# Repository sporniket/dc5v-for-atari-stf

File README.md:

# DC5V for the Atari STF

> [WARNING] Please read carefully this note before using this project. It contains important facts.

Content

1. What is **DC5V for the Atari STF**, and when to use it ?
2. What should you know before using **DC5V for the Atari STF** ?
3. How to use **DC5V for the Atari STF** ?
4. Known issues
5. Miscellanous

## 1. What is **DC5V for the Atari STF**, and when to use it ?

**DC5V for the Atari STF** is an alternative pcb to replace the integrated power supply of the Atari STf, based on the premise that the original power plug will receive a DC 5V, 3A to 4A supply instead of being plugged to the main grid (110V to 240V, 50Hz to 60Hz, 1A).

**BOM v1**

|Designator|Description|URL (if appliable)|
|---|---|---|
|J1|**Würth Elektronik** 7.00mm Screwless 45° Entry, Serie 4122, 1×3 – #691412220003|[Mouser 710-691412220003](https://www.mouser.com/ProductDetail/710-691412220003) |
|F1|**Würth Elektronik** Shocksafe Fuse Holder – #696310001002|[Mouser 710-696310001002](https://www.mouser.com/ProductDetail/710-696310001002) |
|SW1|Latching Push Button, on-off Switch, DIP 6 pins (row pitch 6mm, pin pitch 2.5mm, 8×8mm body)|[Aliexpress 1005003333312190](https://www.aliexpress.com/item/1005003333312190.html) |
|J2 - contact|**TE connectivity** Connector Contact, Socket, Wire-to-Board / Wire-to-Wire, 26 – 20 AWG Wire Size, .12 – .5 mm² Wire Size, Tin, Strip, Wire & Cable, 2 A, Signal – #170262-1|[Mouser 571-1702621-CT ](https://www.mouser.com/ProductDetail/571-1702621-CT) |
|J2 - housing|**TE connectivity** Housing, Receptacle, Wire-to-Board, 6 Position, .098in/2.5 mm Centerline, Crimp, 1 Row, Natural, Mating Retention, Wire & Cable, Power & Signal – #171822-6|[Mouser 571-171822-6](https://www.mouser.com/ProductDetail/571-171822-6) |
|J3 - pin sockets|Round socket connector strip|[Exxos #0169](https://www.exxosforum.co.uk/atari/store2/#0169) |
|J3 - pins|Round pin connector strip|[Exxos #0132](https://www.exxosforum.co.uk/atari/store2/#0132) |
|J4|Right angled, pitch 2.54mm, 1×4 pins header|—|
|J5|pitch 2.54mm, 1×2 pins header, classic or JST style|—|

### Licence

**DC5V for the Atari STF** is published under the Creative Commons CC0 license. You can find a copy of the licence there : https://creativecommons.org/publicdomain/zero/1.0/legalcode

You can copy, modify, distribute and perform the work, even for commercial purposes, all without asking permission.

**DC5V for the Atari STF** is distributed in the hope that it will be useful, but WITHOUT ANY WARRANTY; without even the implied warranty of MERCHANTABILITY or FITNESS FOR A PARTICULAR PURPOSE.

### Release notes

## 2. What should you know before using **DC5V for the Atari STF** ?

**DC5V for the Atari STF** is made using Kicad 6.

> Do not use **DC5V for the Atari STF** if this project is not suitable for your project.

## 3. How to use **DC5V for the Atari STF** ?

### From sources

To get the latest available work, one must clone the git repository, build and install the package.

	git clone --recurse-submodules https://github.com/sporniket/dc5v-for-atari-stf.git

Then, open the project with Kicad 6.

## 4. Known issues
See the [project issues](https://github.com/sporniket/dc5v-for-atari-stf/issues) page.

## 5. Miscellanous

### Report issues
Use the [project issues](https://github.com/sporniket/dc5v-for-atari-stf/issues) page.

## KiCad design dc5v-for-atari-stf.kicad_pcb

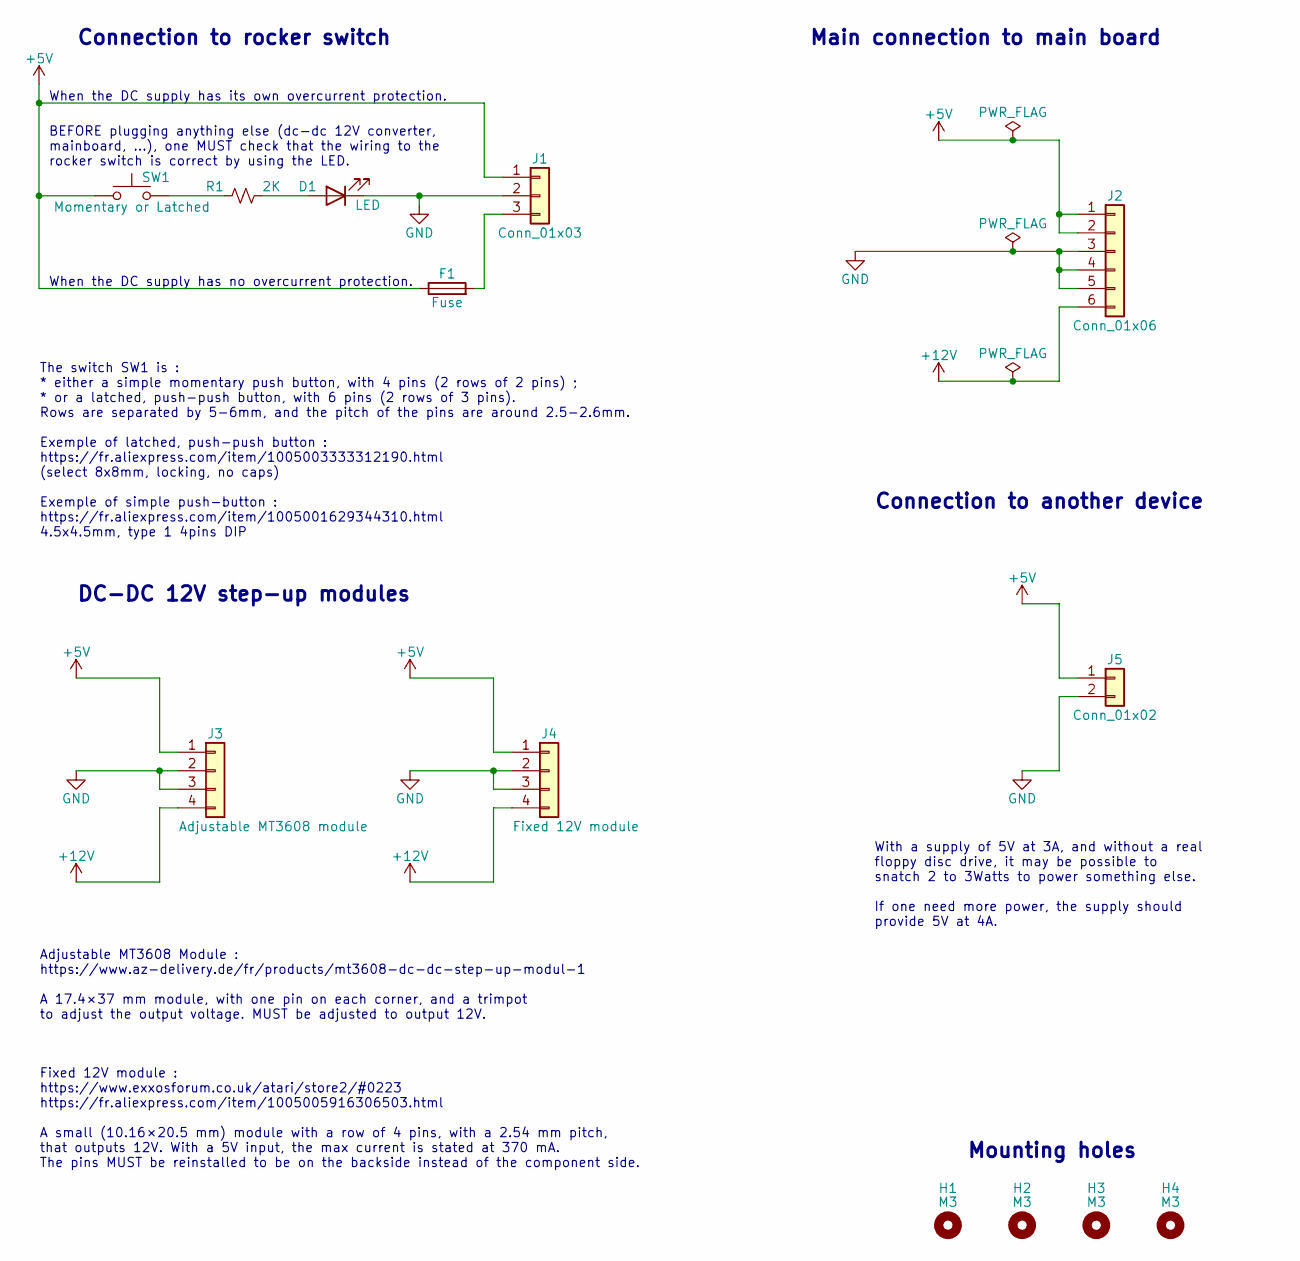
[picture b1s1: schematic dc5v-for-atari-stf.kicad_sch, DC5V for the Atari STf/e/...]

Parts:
D1: LED; LED_D3.0mm
F1: Fuse; FuseHolder_Cylinder_5x20mm_Wurth_Elektronik_696310001002; Mouser part number 710-696310001002
H1, H2, H3, H4: M3; MountingHole_3.5mm
J1: Conn_01x03; Fixed_Terminal_Blocks_Wurth_Elektronik_Serie_4122_7.00mm_Sc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; Mouser part number 710-691412220003
J2: Conn_01x06; PinHeader_1x06_P2.54mm_Vertical
J3: Adjustable MT3608 module; module_mt3608_ajustable_output
J4: Fixed 12V module; module_dc_dc_step_up_12V_W10.16mm_H20.5mm_PinSocket_1x04_P2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
J5: Conn_01x02; PinHeader_1x02_P2.54mm_Vertical
R1: 2K; Passive_THT_resistor_W2.54mm_L12.70mm
SW1: Momentary or Latched; combined_push_button_4pins_X_latched_button_6pins__2rows_W5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

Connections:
+5V: F1.1, J1.1, J2.1, J2.2, J3.1, J4.1, J5.1, SW1.1
+12V: J2.6, J3.4, J4.4
GND: D1.1 (K), J1.2, J2.3, J2.4, J2.5, J3.2, J3.3, J4.2, J4.3, J5.2
unnamed: D1.2 (A), R1.2
unnamed: F1.2, J1.3
unnamed: R1.1, SW1.2

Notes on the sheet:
The switch SW1 is : * either a simple momentary push button, with 4 pins (2 rows of 2 pins) ; * or a latched, push-push button, with 6 pins (2 rows of 3 pins). Rows are separated by 5-6mm, and the pitch of the pins are around 2.5-2.6mm. Exemple of latched, push-push button : https://fr.aliexpress.c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
Mounting holes
With a supply of 5V at 3A, and without a real floppy disc drive, it may be possible to snatch 2 to 3Watts to power something else. If one need more power, the supply should provide 5V at 4A.
DC-DC 12V step-up modules
Connection to rocker switch
BEFORE plugging anything else (dc-dc 12V converter, mainboard, ...), one MUST check that the wiring to the rocker switch is correct by using the LED.
Main connection to main board
When the DC supply has its own overcurrent protection.
Connection to another device
Adjustable MT3608 Module : https://www.az-delivery.de/fr/products/mt3608-dc-dc-step-up-modul-1 A 17.4×37 mm module, with one pin on each corner, and a trimpot to adjust the output voltage. MUST be adjusted to output 12V.
Fixed 12V module : https://www.exxosforum.co.uk/atari/store2/#0223 https://fr.aliexpress.com/item/1005005916306503.html A small (10.16×20.5 mm) module with a row of 4 pins, with a 2.54 mm pitch, that outputs 12V. With a 5V input, the max current is stated at 370 mA. The pins MUST be reinstalled to 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
When the DC supply has no overcurrent protection.

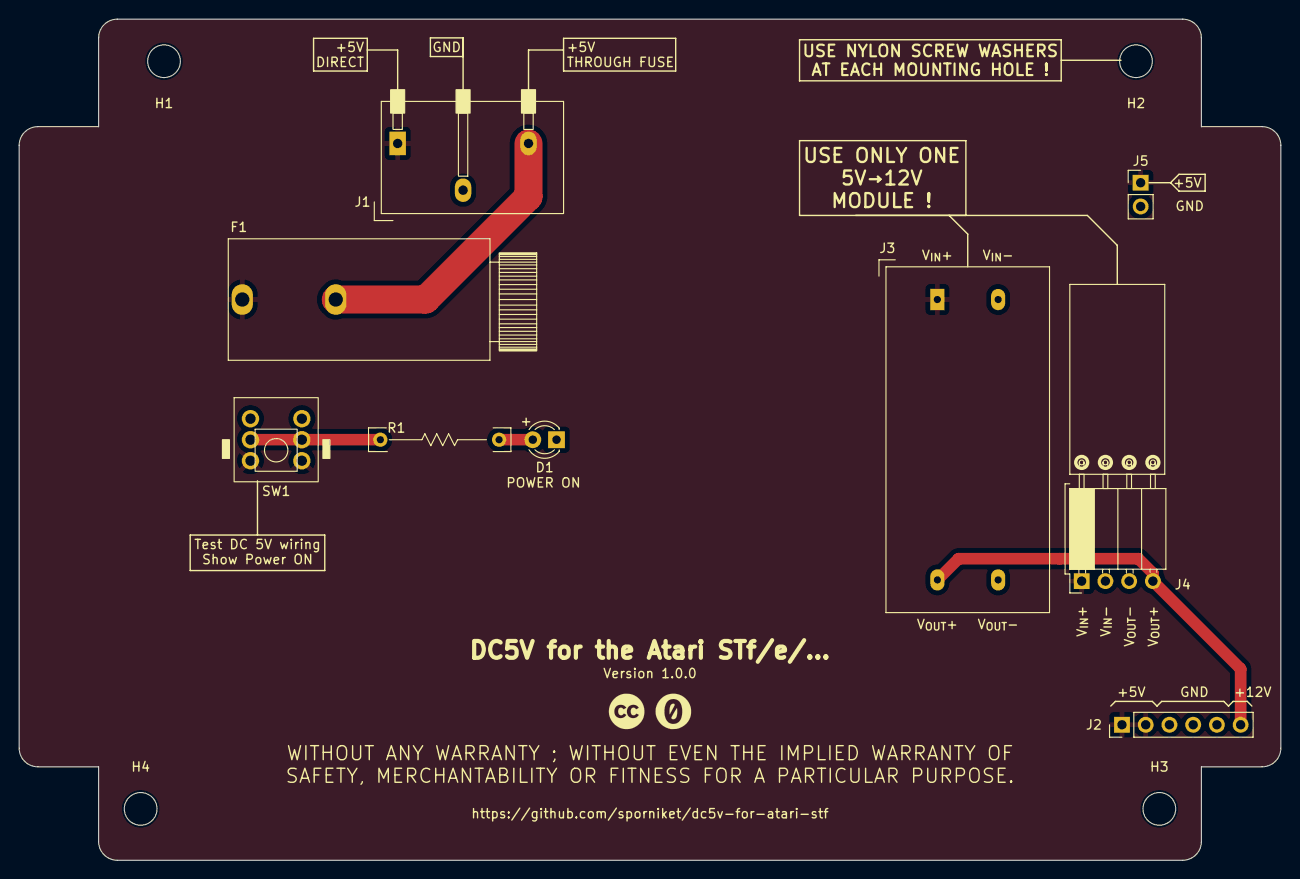
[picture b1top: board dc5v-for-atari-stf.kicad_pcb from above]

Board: 2 copper layers, 135.0 x 90.0 mm, 13 parts (0 on the bottom side), 6 nets.

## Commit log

2023-08-21 update submodules : kicad-symbols-handmade and kicad-footprints-handmade
2023-08-22 init readme
2023-08-22 initialize project
2023-08-22 do the schematic
2023-08-22 metadata of the schematic
2023-08-22 added footprints library for power modules
2023-08-22 Numbers on symbols, add footprint so that SW1 can be either push button or latched push-push button
2023-08-23 update footprint libraries : terminal blocks - Wurth Elektronik serie 4122 - 7mm screwless 45 degrees - 2 pins
2023-08-23 updated footprint : combined_push_button_4pins_X_latched_button_6pins__2rows_W5_6mm_pitch_2.5_2.6mm
2023-08-23 associating footprints
2023-08-23 add pcb : template of the shape of the pcb
2023-08-23 pcb : layout, pcb edges
2023-08-23 pcb : label to show polarisation/voltages
2023-08-24 schematic : provide alternative path to rocker switch, to optionnally protect with a fuse
2023-08-24 added footprints : Fixed terminal blocks 1x3, shocksafe 5x20mm fuse holder
2023-08-24 schematic : associate footprints to J1 and F1
2023-08-24 pcb : rework using updates
2023-08-24 pcb : tweak label position
2023-08-24 Additionnal markings, tweaks on labels,...
2023-08-24 add references to part numbers
2023-08-25 BOM for the v1 series
2023-08-25 readme : fixed formatting
2023-08-25 readme : fixed formatting, again
2023-08-25 tweak labels
2023-08-26 bump version
2023-08-26 additionnal marking
2023-08-26 prepare next release
2023-09-29 migrate to Kicad 7
2023-10-15 Various fixes toward final releases : block terminal footprint and positionning, labels
2023-10-31 finalise v1.0.0
